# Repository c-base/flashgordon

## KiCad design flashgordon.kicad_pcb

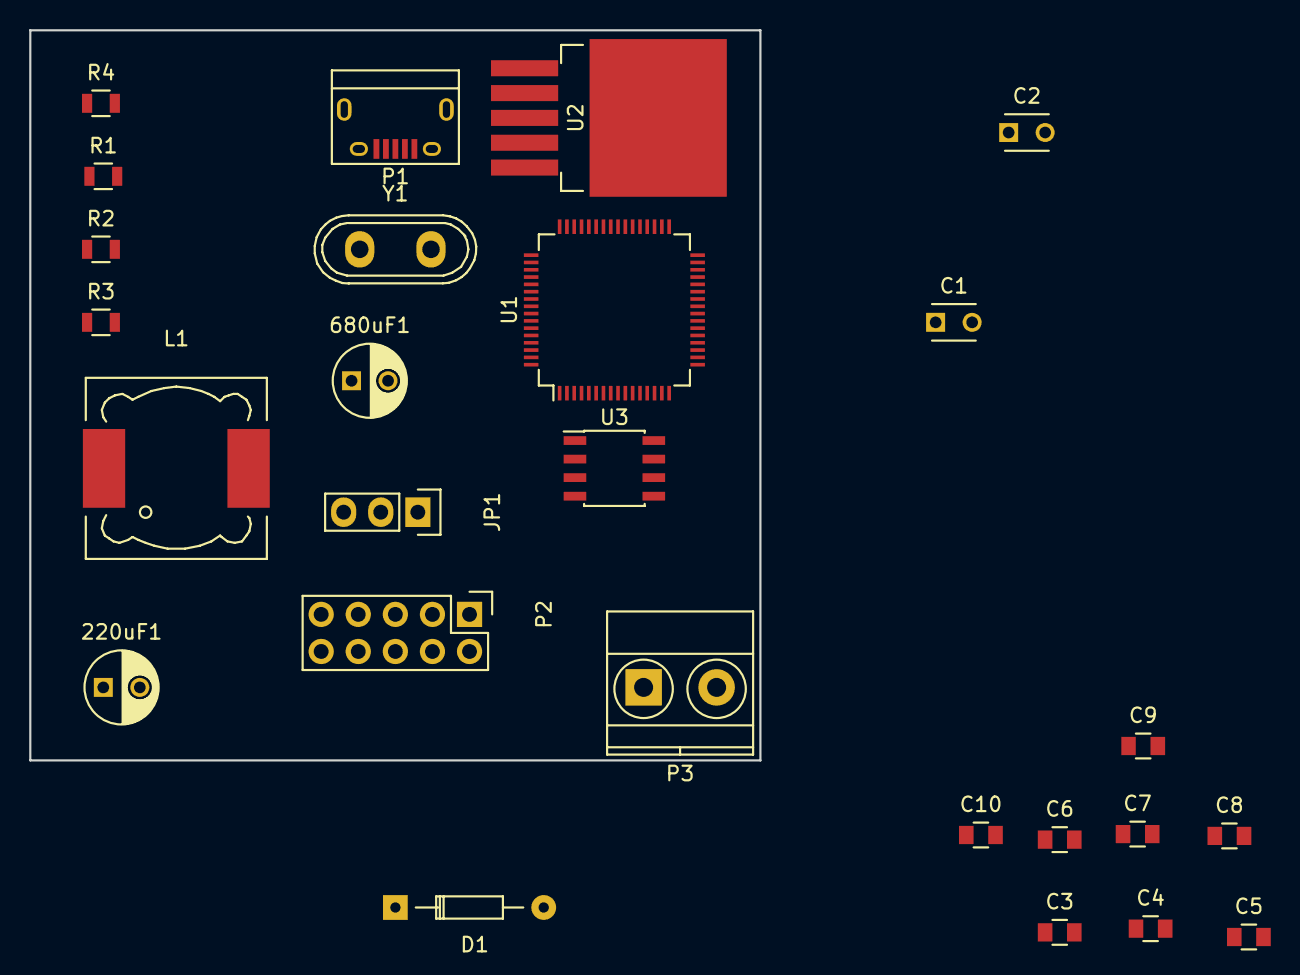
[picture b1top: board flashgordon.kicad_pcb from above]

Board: 2 copper layers, 50.0 x 50.0 mm, 26 parts (0 on the bottom side), 21 nets, no tracks yet.

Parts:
220uF1, 680uF1: C; C_Radial_D5_L6_P2.5
C1, C2: 27pF; C_Disc_D3_P2.5
C3, C4, C5, C6, C7, C8, C9: 100nF; C_0805
C10: 3.3uF; C_0805
D1: 1N5824; Diode_DO-35_SOD27_Horizontal_RM10
JP1: JUMPER3; Pin_Header_Straight_1x03
L1: INDUCTOR; Choke_SMD_12x12mm_h8mm
P1: USB_OTG; USB_Micro-B
P2: SPI-Clip; Pin_Header_Straight_2x05
P3: Thinkpad 20V Connector; TerminalBlock_Pheonix_MKDS1.5-2pol
R1: 12K; R_0805
R2: 1K; R_0805
R3: 10K; R_0805
R4: 2.2K; R_0805
U1: FT2232HL; LQFP-64_10x10mm_Pitch0.5mm
U2: LM2596S-3.3; TO-263-5Lead
U3: 93CxxC; SOIC-8_3.9x4.9mm_Pitch1.27mm
Y1: 12MHz; Crystal_HC50-U_Vertical

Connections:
+3V3: 220uF1.1, C6.1, C7.1, C8.1, C9.1, L1.1, P2.3, P2.8, R2.1, R3.1, U1.4, U1.9, U1.20, U1.31, U1.42, U1.50, U1.56, U2.4, U3.6, U3.8
+24V: JP1.1, P3.2
/DM: P1.2, U1.7
/DP: P1.3, U1.8
/VCORE: C3.1, C4.1, C5.1, C10.1, U1.12, U1.37, U1.49, U1.64
GND: 220uF1.2, 680uF1.2, C1.2, C2.2, C3.2, C4.2, C5.2, C6.2, C7.2, C8.2, C9.2, C10.2, D1.2, P1.5, P2.4, P3.1, R1.2, U1.1, U1.5, U1.10, U1.11, U1.13, U1.15, U1.25, U1.35, U1.47, U1.51, U2.3, U2.5, U3.5
unnamed: 680uF1.1, JP1.2, U2.1
unnamed: C1.1, U1.2, Y1.2
unnamed: C2.1, U1.3, Y1.1
unnamed: D1.1, L1.2, U2.2
unnamed: JP1.3, P1.1
unnamed: P2.1, U1.19
unnamed: P2.2, R3.2, U1.17
unnamed: P2.5, U1.18
unnamed: P2.6, U1.16
unnamed: R1.1, U1.6
unnamed: R2.2, U1.14
unnamed: R4.1, U1.61, U3.3
unnamed: R4.2, U3.4
unnamed: U1.62, U3.2
unnamed: U1.63, U3.1

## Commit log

2016-05-28 kicad project generated. AHHHHHHH!
2016-05-28 FLASH! AHHHHH!
2016-08-21 draw circuit
2016-08-27 add LM2596
2016-09-09 basic schematic done
2016-09-10 add basic pcb
2016-09-10 add diode
